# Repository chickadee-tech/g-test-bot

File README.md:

# Chickadee Tech Acro Polystack Mod #
This is the bottom of the test jig for Polystack **control** and **mod** boards.

## Documentation ##
See the [wiki](https://github.com/chickadee-tech/g-test-bot/wiki) for documentation.

## Polystack ##
This board is part of the Polystack platform for modular microcontrol systems. More information on the platform can be found at [polystack.org](http://polystack.org).

## Support ##
If you need support with a board you own or have development questions please email support@chickadee.tech or check [chickadee.tech/support](https://chickadee.tech/support) for other ways to get support.

## Contributing ##
Please note that this project is released with a [Contributor Code of Conduct](CODE_OF_CONDUCT.md). By participating in this project you agree to abide by its terms.

### Setup ###
Components and footprints for PCB parts are not included in this repository. Instead, checkout the [chickadee-tech/kicad-libs](https://github.com/chickadee-tech/kicad-libs) repository in the same directory that this repository is checked out in. All part definitions should be relative so that they will load correctly.

### Pull requests ###
For fixes please submit a pull request to the original repository. After the pull request is merged, check the [Chickadee Tech Active Contributor Discount (ACD)](https://chickadee.tech/active-contributor) to see if you are eligible for a discount code to use on your next purchase.

### Derivatives ###
If developing your own version of the test jig bottom board please remove all Chickadee Tech trademarks and follow the [CC-BY license](pcb/LICENSE) for the PCB and the MIT license for the code. While not required, please consider open sourcing your modifications so others can learn from your improvements. If you do email support@chickadee.tech and we may choose to add your project to the ACD.

You may also license the Polystack logo for free by emailing support@chickadee.tech. We'll ask for your gerbers to ensure the design complies with specifications laid out [here](https://github.com/chickadee-tech/polystack/wiki) and provide written permission to use the trademark after compliance has been demonstrated.

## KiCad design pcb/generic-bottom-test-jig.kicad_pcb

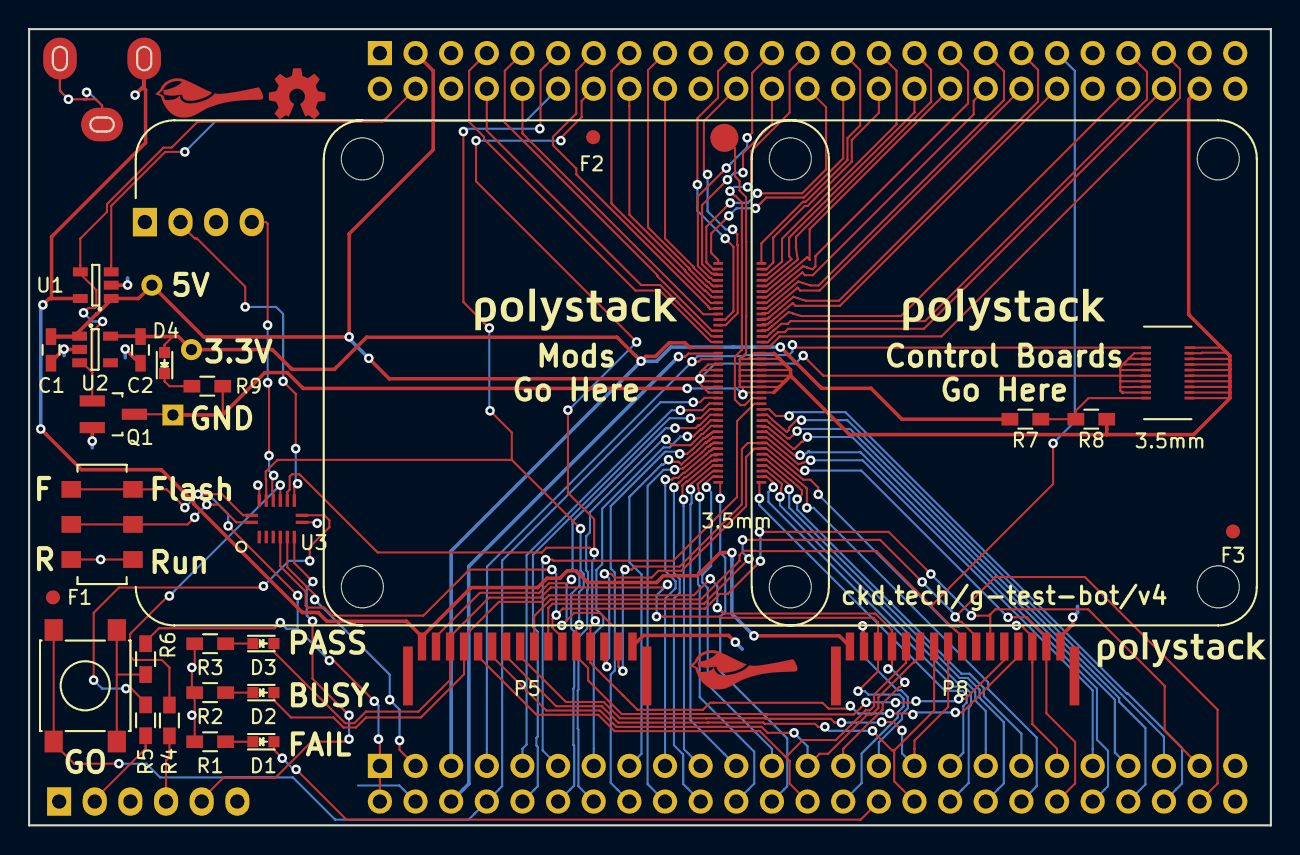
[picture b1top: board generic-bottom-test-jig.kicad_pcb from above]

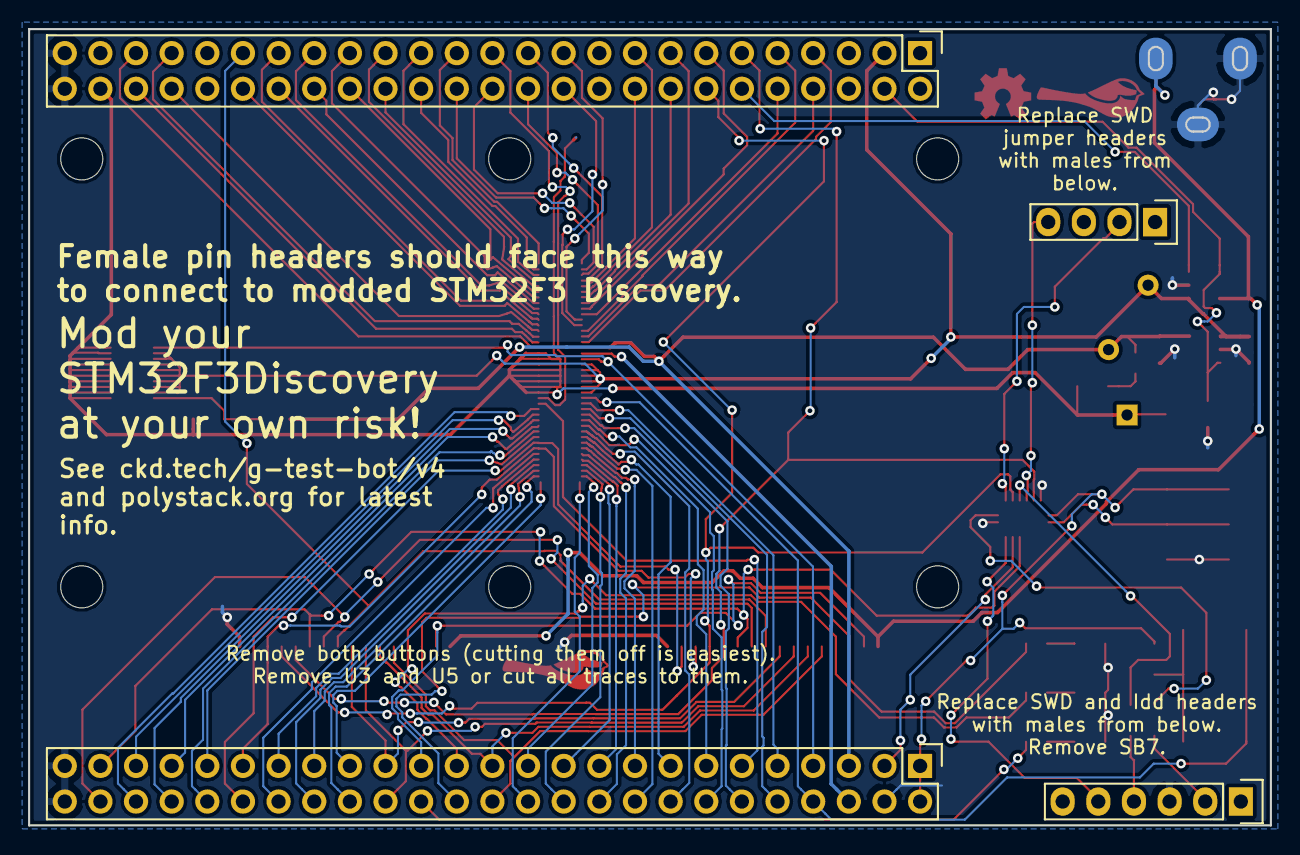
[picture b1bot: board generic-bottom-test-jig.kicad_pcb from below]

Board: 2 copper layers, 88.5 x 56.8 mm, 40 parts (4 on the bottom side), 101 nets.

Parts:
C1: 2.2uF; C_0603_HandSoldering
C2: 1uF; C_0603_HandSoldering
CON1: BARREL_JACK; PJ-037BH-SMT-OVAL-EDGE
D1, D4: RED; LED_0603
D2: YELLOW; LED_0603
D3: GREEN; LED_0603
F1, F2, F3: 1mm; Fiducial
P1: CONN_01X06; Pin_Header_Straight_1x06
P2, P4: CONN_02X25; Pin_Header_Straight_2x25
P3: CONN_01X04; Pin_Header_Straight_1x04
P5, P8: CONN_01X16; SFW12LF-16pin
P6: CONN_02X10; DF40-1.5mm-20pin-Receptacle
P7: CONN_01X01; 0910
P9, P10: CONN_01X01; Measurement_Point_Round-TH_Small
P11: CONN_01X01; Measurement_Point_Square-TH_Small
PORT_OUT1: CKD_SANDWICH; DF40-3-4mm-80pin-Receptacle
Q1: Q_NMOS_GSD; SOT-23_Handsoldering
R1, R2, R3, R9: 1k; R_0603_HandSoldering
R4, R5: 0; R_0603_HandSoldering
R6: 220; R_0603_HandSoldering
R7, R8: 10k; R_0603_HandSoldering
SW1: Switch_SPDT_x2; CL-SB-22B
SW2: SPST; SW_SPST_PTS645
U1: STMPS2151; SOT-23-5
U2: TLV70233DBV; SOT-23-5
U3: 74LS257; SOT763-1(DHVQFN16)
svg2mod, svg2mod#2: G***; polystack-bold-0.75
svg2mod#3: G***; polystack-bold-0.625

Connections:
+5V: CON1.1, P5.1, P8.1, U1.5
/HOST_SWCLK: P3.2, U3.10
/HOST_SWDIO: P3.4, U3.13
/HOST_nRST: P2.3, U3.6
/PA0_MEZ_RESET: P2.11, PORT_OUT1.66
/PA1: P2.10, PORT_OUT1.27
/PA2: P2.13, PORT_OUT1.29
/PA3: P2.12, PORT_OUT1.28
/PA4: P2.15, PORT_OUT1.32
/PA5_SCL: P2.16, PORT_OUT1.31
/PA6_SDO: P2.17, PORT_OUT1.34
/PA7_SDA: P2.18, PORT_OUT1.33
/PA8: P4.46, PORT_OUT1.55
/PA9: P4.43, PORT_OUT1.54
/PA10: P4.44, PORT_OUT1.53
/PA13_SWDIO: P4.39, P5.9, P8.9
/PA14_SWCLK: P4.38, PORT_OUT1.50
/PA15: P4.37, PORT_OUT1.51
/PB0: P2.21, PORT_OUT1.37
/PB1: P2.22, PORT_OUT1.38
/PB2: P2.23, PORT_OUT1.39
/PB3_SWO_MEZ_BOOT: P4.25, PORT_OUT1.65
/PB4: P4.24, PORT_OUT1.3
/PB5: P4.23, PORT_OUT1.4
/PB6_SCL: P4.22, PORT_OUT1.12
/PB7_SDA: P4.21, PORT_OUT1.11
/PB8: P4.18, PORT_OUT1.5
/PB9: P4.17, PORT_OUT1.6
/PB10: P2.33, PORT_OUT1.80
/PB11: P2.34, PORT_OUT1.79
/PB12: P2.35, PORT_OUT1.78
/PB13: P2.36, PORT_OUT1.77
/PB14: P2.37, PORT_OUT1.76
/PB15: P2.38, PORT_OUT1.75
/PC0_3V3: C2.1, D4.2, P2.5, P10.1, PORT_OUT1.16, R7.1, U2.5
/PC1_3V3_E: P2.6, PORT_OUT1.17
/PC2_BATT: P2.7, P6.19, PORT_OUT1.18
/PC3_SWITCH: P2.8, PORT_OUT1.25, SW2.1
/PC4: P2.19, PORT_OUT1.36
/PC5: P2.20, PORT_OUT1.35
/PC6_BOOT0: P2.48, P5.10, P8.10
/PC7_RESET: P2.47, P5.11, P8.11, U3.5
/PC8_GND: P4.48, P6.2, P6.4, P6.6, P6.8, P6.10, P6.12, P6.14, P6.16, P6.18, P6.20, P7.1, P11.1, PORT_OUT1.57, PORT_OUT1.58, PORT_OUT1.59, PORT_OUT1.60, PORT_OUT1.61, PORT_OUT1.62, PORT_OUT1.63, PORT_OUT1.64, Q1.3, R8.2, R9.2
/PC9: P4.45, PORT_OUT1.56
/PC10: P4.36, PORT_OUT1.48
/PC11: P4.35, PORT_OUT1.49
/PC12: P4.34, PORT_OUT1.46
/PC13: P4.9, PORT_OUT1.13
/PC14: P4.8, PORT_OUT1.14
/PC15: P4.7, PORT_OUT1.15
/PD0: P4.33, PORT_OUT1.47
/PD1: P4.32, PORT_OUT1.44
/PD2: P4.31, PORT_OUT1.45
/PD3: P4.30, PORT_OUT1.42
/PD4: P4.29, PORT_OUT1.43
/PD5: P4.28, PORT_OUT1.1
/PD6: P4.27, PORT_OUT1.41
/PD7: P4.26, PORT_OUT1.2
/PD8_TX: P2.39, P5.14, P8.14, PORT_OUT1.74
/PD9_RX: P2.40, P5.15, P8.15, PORT_OUT1.73
/PD10: P2.41, PORT_OUT1.72
/PD11: P2.42, PORT_OUT1.71
/PD12: P2.43, PORT_OUT1.70
/PD13: P2.44, PORT_OUT1.69
/PD14: P2.45, PORT_OUT1.68
/PD15: P2.46, PORT_OUT1.67
/PE0: P4.16, PORT_OUT1.7
/PE1: P4.15, PORT_OUT1.8
/PE3: P4.13, PORT_OUT1.9
/PE4_FAULT: P4.12, U1.3
/PE6: P4.10, PORT_OUT1.10
/PE7: P2.24, PORT_OUT1.40
/PE8_LD4_BLUE: P2.25, P5.6, P8.6
/PE9_LD3_RED: P2.26, P5.5, P8.5
/PE10_LD5_ORANGE: D2.2, P2.27, P5.4, P8.4
/PE11_LD7_GREEN: D3.2, P2.28, P5.3, P8.3
/PE12_LD9_BLUE: P2.29, P5.2, P8.2
/PE13_LD10_RED: D1.2, P2.30
/PE14_LD8_ORANGE: P2.31, P5.8, P8.8
/PE15_LD6_GREEN: P2.32, P5.7, P8.7
/PF2: P2.9, PORT_OUT1.26
/PF4: P2.14, PORT_OUT1.30
/PF6: P4.40, PORT_OUT1.52
/PF9_POWER_ENABLE: P4.4, Q1.1, U1.4, U2.3
/PF10_5V: C1.1, P4.3, P6.3, P6.5, P6.7, P6.9, P6.11, P6.13, P6.15, P6.17, P9.1, PORT_OUT1.19, PORT_OUT1.20, PORT_OUT1.21, PORT_OUT1.22, PORT_OUT1.23, PORT_OUT1.24, U1.1, U2.1
/SWCLK: R5.1, U3.9
/SWDIO: R4.2, U3.12
/SWD_SELECT: SW1.2, SW1.5, U3.1
/TEST_SWCLK: P4.14, P5.13, P8.13, U3.11
/TEST_SWDIO: P4.11, P5.12, P8.12, U3.14
/nRST: P1.5, U3.7
GND: C1.2, C2.2, CON1.2, CON1.3, P1.3, P2.4, P2.49, P2.50, P4.49, P4.50, P5.16, P8.16, Q1.2, R1.2, R2.2, R3.2, SW1.3, SW1.6, U1.2, U2.2, U3.8, U3.15
unnamed: D1.1, R1.1
unnamed: D2.1, R2.1
unnamed: D3.1, R3.1
unnamed: D4.1, R9.1
unnamed: P1.2, R5.2
unnamed: P1.4, R4.1
unnamed: P6.1, R7.2, R8.1
unnamed: R6.2, SW2.2
VCC: P2.1, P2.2, R6.1, SW1.1, SW1.4, U3.16

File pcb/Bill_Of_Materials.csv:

part name,symbol,size (imp),max current,unit price,units per build,units in stock,order total,Manufacturer ID,source url,datasheet,datasheet2,,,
C 2.2uF,C1,603,,$0.05,1,92,$0.05,C0603C225K9PACTU,http://www.digikey.com/product-detail/en/C0603C225K9PACTU/39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,,,,Total Base Cost,$51.09
C 1uF X7R,C2,603,,$0.03,1,20,$0.03,TMK107B7105KA-T,http://www.digikey.com/product-detail/en/TMK107B7105KA-T/587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,MF-CAP-0603-1uF,http://ds.yuden.co.jp/TYCOMPAS/ut/detail.do?productNo=TMK107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,price ranges 1.40 - 2.50,,
barrel jack smd,CON1,,,$1.18,1,1,$1.18,PJ-102AH,http://www.digikey.com/product-search/en?keywords=PJ-102AH,N,,,,
red led,D1,,,$0.19,1,71,$0.19,LTST-C190KRKT,http://www.digikey.com/product-detail/en/LTST-C190KRKT/160-1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,MF-LED-0603-RED,http://optoelectronics.liteon.com/upload/download/DS-22-99-0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,,,
yellow led,D2,,,$0.20,1,87,$0.20,LTST-C190KSKT,http://www.digikey.com/product-detail/en/LTST-C190KSKT/160-1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,N,http://optoelectronics.liteon.com/upload/download/DS-22-99-0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,,,
green led,D3,,,$0.19,1,83,$0.19,LTST-C190KGKT,http://www.digikey.com/product-detail/en/LTST-C190KGKT/160-1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,Y,http://optoelectronics.liteon.com/upload/download/DS22-2000-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,,,
1x6 Female 5mm Tin,P1,,,$1.20,1,1,$1.20,CES-106-01-T-S,http://www.digikey.com/product-detail/en/CES-106-01-T-S/SAM1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,N,http://suddendocs.samtec.com/prints/ces-dmkt.pdf,,,
2x25 Female 5mm Tin,"P2, P4",,,$4.54,2,0,$9.08,CES-125-01-T-D,http://www.digikey.com/product-detail/en/CES-125-01-T-D/SAM1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,N,http://suddendocs.samtec.com/prints/ces-dmkt.pdf,,,
1x4 Female 5mm Gold,P3,,,$2.37,1,1,$2.37,CES-104-01-S-S,http://www.digikey.com/product-detail/en/CES-104-01-S-S/SAM1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,N,http://suddendocs.samtec.com/prints/ces-dmkt.pdf,,,
side entry top 16pos 1mm,"P5, P8",,,$0.80,2,1,$1.60,SFW16R-2STE1LF,http://www.digikey.com/product-detail/en/SFW16R-2STE1LF/609-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,N,,,,
20 pin receptacle (3.5mm),P6,,,$0.78,1,0,$0.78,DF40HC(3.5)-20DS-0.4V(51),,N,http://www.hirose.co.jp/cataloge_hp/ed_DF40_20140305.pdf,,,
3.5mm pogopin,P7,,,$1.41,1,0,$1.41,0910-8-57-20-76-14-11-0,http://www.digikey.com/product-detail/en/0910-8-57-20-76-14-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,N,https://www.mill-max.com/assets/pdfs/metric/026M.pdf,,,
80 pin receptacle (3.5mm),PORT_OUT1,,0.3A a pin,$2.42,1,1,$2.42,DF40HC(3.5)-80DS-0.4V(51),http://www.digikey.com/product-detail/en/DF40HC(3.5)-80DS-0.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,N,http://www.hirose.co.jp/cataloge_hp/ed_DF40_20140305.pdf,,,
n-channel mosfet,Q1,"TO-236-3, SC-59, SOT-23-3",220mA continuous,$0.09,1,59,$0.09,BSS138,http://www.digikey.com/product-detail/en/BSS138/BSS138CT-ND/244294,MF-DSC-SOT233-BSS138,https://www.fairchildsemi.com/datasheets/BS/BSS138.pdf,,,
R 1k,"R1, R2, R3",603,,$0.01,3,993,$0.03,RC0603FR-071KL,http://www.digikey.com/product-detail/en/RC0603FR-071KL/311-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,MF-RES-0603-1K,http://www.yageo.com/NewPortal/yageodocoutput?fileName=/pdf/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,,,
R 0,"R4, R5",603,,$0.00,2,92,$0.01,RC0603JR-070RL,http://www.digikey.com/product-search/en?keywords=311-0.0grct-nd,,,,,
dpdt,SW1,,200mA,$1.35,1,0,$1.35,CL-SB-22B-02T,http://www.digikey.com/product-detail/en/CL-SB-22B-02T/563-1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,N,http://www.nidec-copal-electronics.com/e/catalog/switch/cl-sb.pdf,,,
tactile switch top,SW2,,,$0.24,1,3,$0.24,PTS645SK50SMTR92 LFS,http://www.digikey.com/product-search/en?keywords=ckn9087ct-nd,MF-SW-TACT-6MM,,,,
high side power switch,U1,sot23-5,500mA,$0.65,1,0,$0.65,STMPS2151STR,http://www.digikey.com/product-detail/en/STMPS2151STR/497-69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,N,http://www.st.com/web/en/resource/technical/document/datashe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,,,
3.3v regulator,U2,SOT23-5,0.3A,$0.49,1,8,$0.49,TLV70233DBVR,http://www.digikey.com/product-detail/en/TLV70233DBVR/296-32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,MF-REG-SOT235-3.3V-300mA,http://www.ti.com/lit/ds/symlink/tlv702.pdf,,,
4 x 1:2,U3,16-VFQFN Exposed Pad,,$0.63,1,1,$0.63,"74CBTLV3257BQ,115","http://www.digikey.com/product-detail/en/nxp-semiconductors/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,115/568-5423-1-ND/2530901",N,http://www.nxp.com/documents/data_sheet/74CBTLV3257.pdf,,,
Generic Bottom Test Jig,Off board,,,$13.03,1,3,$13.03,CKD-G-TEST-BOT-V2,,N,,,,
STM32F3Discovery,STM32 F3 Discovery,,,$11.57,1,1,$11.57,STM32F3Discovery,http://www.digikey.com/product-search/en?keywords=stm32f3discovery,N,http://www.st.com/st-web-ui/static/active/en/resource/techni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,,,
Nylon Hex Nut,Off board,,,$0.10,4,94,$0.38,4688,http://www.mouser.com/ProductDetail/Keystone-Electronics/468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,N,http://www.mouser.com/ds/2/215/688-744520.pdf,,,
~1.25mm Spacer,Off Board,,,$0.08,4,8,$0.34,908-050,,N,,,,
"6"" Premo Flex 16 pos FPC",Off board,,,$1.56,1,1,$1.56,98267-0321,http://www.digikey.com/product-detail/en/molex-llc/021039031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,,,,,
R 220,"R4, R5, R6",603,,$0.00,3,493,$0.01,RC0603JR-07220RL,http://www.digikey.com/product-detail/en/yageo/RC0603JR-0722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,MF-RES-0603-220,http://www.yageo.com/NewPortal/yageodocoutput?fileName=/pdf/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,,,
R 10k,"R7, R8",603,,$0.01,2,979,$0.02,RC0603FR-0710KL,http://www.digikey.com/product-detail/en/RC0603FR-0710KL/311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,MF-RES-0603-10K,http://www.yageo.com/NewPortal/yageodocoutput?fileName=/pdf/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,,,

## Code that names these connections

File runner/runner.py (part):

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}

PIN_TO_FS = {
  "PD5": "TIM1",
  "PD7": "TIM2",
  "PB4": "TIM3",
  "PB5": "TIM4",
  "PB8": "GPIO1",
  "PB9": "GPIO2",
  "PE0": "GPIO3",
  "PE1": "GPIO4",
  "PE3": "GPIO5",
  "PE6": "GPIO6",
  "PB7": "i2c_SDA",
  "PB6": "i2c_SCL",
  "PC13": "HEIGHT_4",
  "PC14": "HEIGHT_2",
  "PC15": "HEIGHT_1",
  "PC0": "3V3_0.3A_LL",
  "PC1": "3V3_0.3A_E",
  "PC2": "+BATT",
  "PF10": "5V",
  "PC3": "UART8_TX",
  "PF2": "UART8_RX",
  "PA1": "UART7_TX",
  "PA3": "UART7_RX",
  "PA2": "UART6_TX",
  "PF4": "UART6_RX",
  "PA5": "UART5_TX",
  "PA4": "UART5_RX",
  "PA7": "UART4_TX",
  "PA6": "UART4_RX",
  "PC5": "UART3_TX",
  "PC4": "UART3_RX",
  "PB0": "UART2_TX",
  "PB1": "UART2_RX",
  "PB2": "UART1_TX",
  "PE7": "UART1_RX",

  "PD6": "TIMG1_CH1",
  "PD3": "TIMG1_CH2",
  "PD4": "TIMG1_CH3",
  "PD1": "TIMG1_CH4",
  "PD2": "TIMG2_CH1",
  "PC12": "TIMG2_CH2",
  "PD0": "TIMG2_CH3",
  "PC10": "TIMG2_CH4",
  "PC11": "ADC1",
  "PA14": "ADC2",
  "PA15": "SDMMC1_D0",
  "PF6": "SDMMC1_D1",
  "PA10": "SDMMC1_D2",
  "PA9": "SDMMC1_D3",
  "PA8": "SDMMC1_CK",
  "PC9": "SDMMC1_CMD",
  "PC8": "GND",
  "PB3": "BOOT0",
  "PA0": "RESET",
  "PD15": "CAN_HI",
  "PD14": "CAN_LO",
  "PD13": "SPI3_NSS",
  "PD12": "SPI3_SCK",
  "PD11": "SPI3_MISO",
  "PD10": "SPI3_MOSI",
  "PD9": "SPI2_NSS",
  "PD8": "SPI2_SCK",
  "PB15": "SPI2_MISO",
  "PB14": "SPI2_MOSI",
  "PB13": "SPI1_NSS",
  "PB12": "SPI1_SCK",
  "PB11": "SPI1_MISO",
  "PB10": "SPI1_MOSI"
}

TOP_IGNORE = ["i2c_SDA", "i2c_SCL", "HEIGHT_2", "HEIGHT_1", "3V3_0.3A_LL", "5V"]

BROKEN_PINS = {"ABoAJ0YzVxEgOTEy": ["UART5_TX"]}

EXPECTED_INTERNAL_HIGH = {"F3FC": ["PA12", "PC13", "PC14", "PC15"], "F4FC": ["PC13", "PC14", "PC15"]}
# TODO(tannewt): Add in 8 and 9 to the expected for the F4FC because they are i2c and should read high.
DEFAULT_TOP_STATE = {"F3FC": "8,9,12,13,16,1001,1003", "F4FC": "8,9,12,13,16,1001,1003"}

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
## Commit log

2016-01-26 Beginnings of the bottom test jig schematic.
2016-01-30 Gerbers for v1 of the test jig.
2016-03-05 Initial versions of embedded test code and python code to run it.
    The model is for the embedded code to be agnostic to what its testing and simply provide commands and output to the python script that controls it. Its the Python's job to make higher level decisions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
2016-03-05 Generic Test Jig Bottom v2 with many changes.
    * Stops sharing power enable funcitonality with addressing.
    * Fixes power connector footprint.
    * Uses a switch to fully change SWD target.
    * Stops using PF0 and PF1 which are connected to the shared oscillator which prevent stable height pins.
    * Moves the barrel connector to allow the debug board to fit.
    * Adds a voltage divider to the current pin on the power connector.
2016-03-21 Get i2c memory read working.
2016-03-22 Support writing to expansion memory and packing expansion info into a protocol buffer.
2016-04-07 Updates to the bottom test jig and addiitonal functionality in runner.
2016-04-13 Rebrand everything to Polystack and increment versions.
2016-04-16 Final gerbers for test manufacturing run.
2016-06-07 Test waiting on the Go button and UART communication to a control board.
2016-06-07 Remove polystack silkscreen tests and add polystack.org URL.
2016-06-17 Many fixes and features to the bottom test jig code.
2016-06-19 Add support for testing F3 control boards.
    Tests include:
    * Testing connectivity from the MCU under test to the Polystack connector.
    * Testing for shorts between internal pins such as the motor outputs.
    * Testing gyro communication and running its self-test.
    The test also logs the unique ID of the MCU and the product ID of the gyro for future reference.
2016-06-19 Generic F4 binary for running on board under test. Nothing actually implemented.
2016-06-19 Working F4 test code. Also keep track of version of test jig code running.
2016-06-24 Lots of work getting the test jig up to snuff.
2016-06-24 Add requirements.txt
2016-06-25 Fixes for running on Windows. Also support checking USB connection after the test jig passes.
2016-06-25 Stop pulling the RESET pin down after Input_Z. It makes the Windows ST Link unhappy because its really undefined behavior that it works otherwise.
2016-06-27 Final production Betaflight binaries for the first batch.
2016-06-29 Correct location of Betaflight bins to flash.
2016-07-06 Runner fixes that fix receiver breakout, USB plug triggering, test device append, and windows ST-LINK location.
2016-07-07 Add license information to many files. PCB design files are CC-BY and code is MIT license.
2016-07-07 Add back .gitignore after repo split.
2016-07-07 Convert to relative component and footprint paths.
2016-07-09 Remove print statement
2016-07-09 Change proto path to match neighboring polystack directory.

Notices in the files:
runner/runner.py:
Copyright (c) 2016 Chickadee Tech LLC
pcb/generic-bottom-test-jig.kicad_pcb:
Copyright 2016 Chickadee Tech LLC,
This work is licensed under the Creative Commons Attribution 4.0 International License.
To view a copy of this license, visit http://creativecommons.org/licenses/by/4.0
or send a letter to Creative Commons, PO Box 1866, Mountain View, CA 94042, USA.
